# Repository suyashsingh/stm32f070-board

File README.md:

# Hardware Board Design for STM32F070F6
`STM32F070F6` is a 32-bit ARM Cortex-M0 microcontroller from ST. This repository contains the hardware files needed for creating a basic board for working with this micro controller. 

EDA Tool: **KiCad(5.0.1)**.

**Many thanks to [Balram](https://www.linkedin.com/in/balram-jatav/) for helping me out with the PCB design :slightly_smiling_face:**

## Images 
1. Real Board - before assembly

2. 3D View of the Board

3. Fab House Front Copper Layer

4. Board Front Copper Layer

## Board Bring Up Checklist
- [x] 1. Change trace width of power tracks
- [x] 2. Merge `dev` branch to master
- [x] 3. Export gerbers - research about fab houses
- [x] 4. Verify gerbers
- [x] 5. Send board to fab house
- [x] 6. Generate BOM
- [x] 7. Order component and tools

## Timeline
| Event                         | Date          |
| ----------------------------- | ------------- |
| Project Start                 | 12 Sep 2019   |
| Schematic Complete            | 5th Oct 2019  |
| Layout Complete               | 6th Oct 2019  |
| Sent gerbers for fabrication  | 3rd Dec 2019  |
| Received PCB's from fab house | 11th Dec 2019 |
| BOM Complete                  | 17th Dec 2019 |
| Ordered Components & Tools    | 17th Dec 2019 |

## Notes
1. Changed the switches with were earlier decided from *robu.in* to [this](https://in.element14.com/alcoswitch-te-connectivity/fsmsm/switch-spst-0-05a-24vdc-smd/dp/1703878) from element14, as mechanical dimensions were not available.

2. Links that might be useful for usb connector:
	+ [Element 14 Page](https://in.element14.com/molex/47346-0001/usb-conn-2-0-micro-usb-type-b/dp/1568026?st=mirco%20usb%20connector)
	+ [Digi Key Kicad Library](https://github.com/Digi-Key/digikey-kicad-library/tree/master/) - Search for MPN
	+ [Mouser](https://www.mouser.in/ProductDetail/Molex/47346-0001?qs=c2CV6XM0DweJBWaSeyWeCw%3D%3D)

3. Always do a board check when you receive the board from the fab house. You can do:
	
	a. Visual Inspection
	
	b. Check for short between the power rails - This board has 3V3 and 5V power rails. Thanks to Balram for pointing out this.

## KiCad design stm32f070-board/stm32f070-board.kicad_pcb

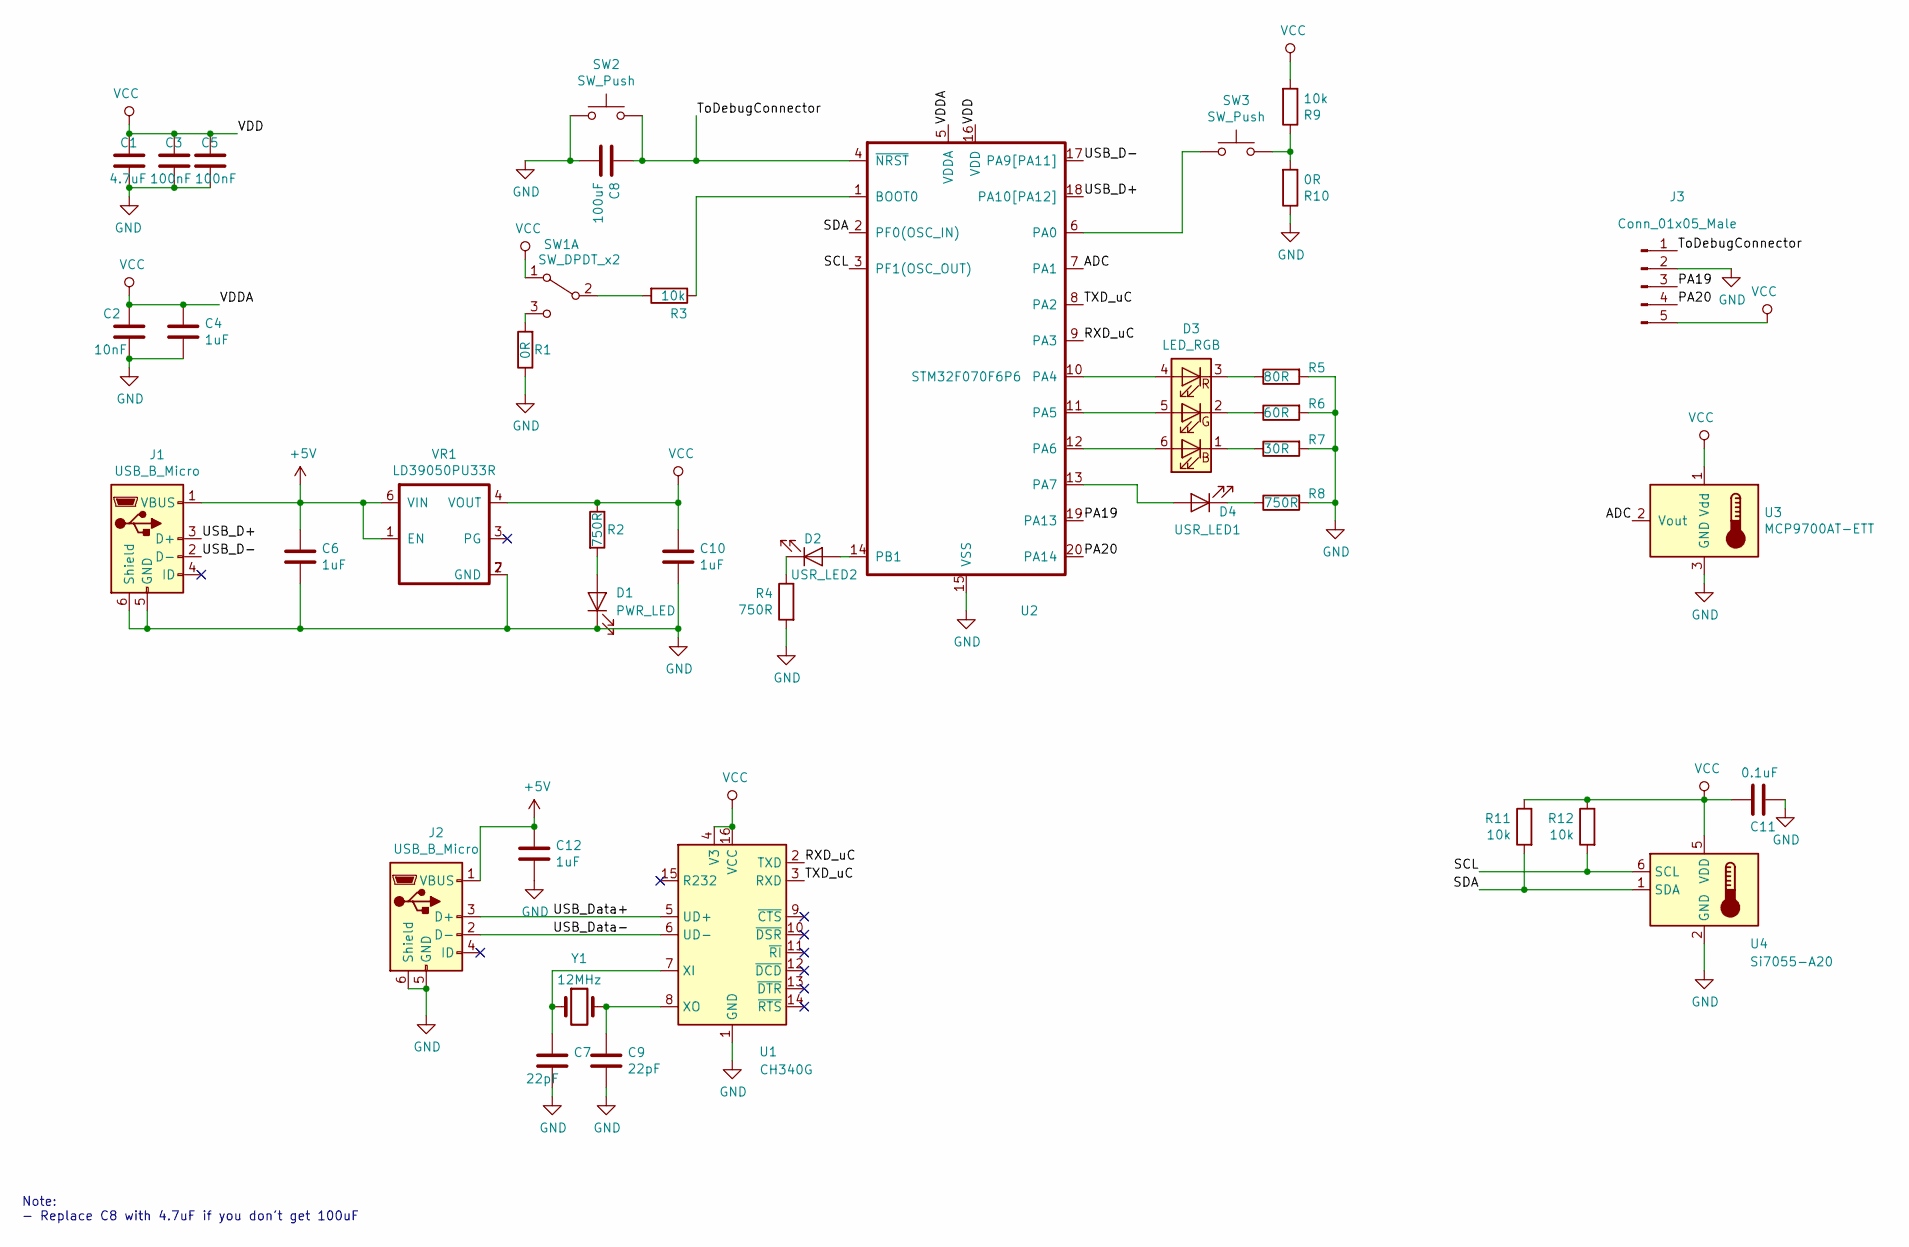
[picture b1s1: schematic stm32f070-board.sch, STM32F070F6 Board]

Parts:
C1: 4.7uF; C_0603_1608Metric_Pad1.05x0.95mm_HandSolder
C2: 10nF; C_0603_1608Metric_Pad1.05x0.95mm_HandSolder
C3, C5: 100nF; C_0603_1608Metric_Pad1.05x0.95mm_HandSolder
C4, C6, C10, C12: 1uF; C_0603_1608Metric_Pad1.05x0.95mm_HandSolder
C7, C9: 22pF; C_0603_1608Metric_Pad1.05x0.95mm_HandSolder
C8: 100uF; C_0603_1608Metric_Pad1.05x0.95mm_HandSolder
C11: 0.1uF; C_0603_1608Metric_Pad1.05x0.95mm_HandSolder
D1: PWR_LED; LED_VISHAY
D2: USR_LED2; LED_VISHAY
D3: LED_RGB; PLCC6
D4: USR_LED1; LED_VISHAY
J1, J2: USB_B_Micro; usb
J3: Conn_01x05_Male; PinHeader_1x05_P1.00mm_Vertical
R1, R10: 0R; R_0603_1608Metric_Pad1.05x0.95mm_HandSolder
R2, R4, R8: 750R; R_0603_1608Metric_Pad1.05x0.95mm_HandSolder
R3, R9, R11, R12: 10k; R_0603_1608Metric_Pad1.05x0.95mm_HandSolder
R5: 80R; R_0603_1608Metric_Pad1.05x0.95mm_HandSolder
R6: 60R; R_0603_1608Metric_Pad1.05x0.95mm_HandSolder
R7: 30R; R_0603_1608Metric_Pad1.05x0.95mm_HandSolder
SW1: SW_DPDT_x2; SLIDE_SWITCH_3.6x9.0mm
SW2, SW3: SW_Push; TACTILE_SWITCH_3.5X6.0mm
U1: CH340G; SOIC-16_3.9x9.9mm_P1.27mm
U2: STM32F070F6P6; TSSOP20_P0.65mm
U3: MCP9700AT-ETT; SOT-23
U4: Si7055-A20; Si705x_Footprint_P1.0mm
VR1: LD39050PU33R; voltage-reg
Y1: 12MHz; HC_49US-(AT49)_1

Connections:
+5V: C6.1, C12.1, J1.1 (VBUS), J2.1 (VBUS), VR1.1 (EN), VR1.6 (VIN)
/ADC: U2.7 (PA1), U3.2 (Vout)
/PA19: J3.3, U2.19 (PA13)
/PA20: J3.4, U2.20 (PA14)
/RXD_uC: U1.2 (TXD), U2.9 (PA3)
/SCL: R12.2, U2.3 (PF1(OSC_OUT)), U4.6 (SCL)
/SDA: R11.2, U2.2 (PF0(OSC_IN)), U4.1 (SDA)
/TXD_uC: U1.3 (RXD), U2.8 (PA2)
/ToDebugConnector: C8.1, J3.1, SW2.2, U2.4 (~NRST)
/USB_D+: J1.3 (D+), U2.18 (PA10[PA12])
/USB_D-: J1.2 (D-), U2.17 (PA9[PA11])
/USB_Data+: J2.3 (D+), U1.5 (UD+)
/USB_Data-: J2.2 (D-), U1.6 (UD-)
GND: C1.2, C2.2, C3.2, C4.2, C5.2, C6.2, C7.2, C8.2, C9.2, C10.2, C11.1, C12.2, D1.1 (K), J1.5 (GND), J1.6 (Shield), J2.5 (GND), J2.6 (Shield), J3.2, R1.1, R4.2, R5.2, R6.2, R7.2, R8.2, R10.1, SW2.1, U1.1 (GND), U2.15 (VSS), U3.3 (GND), U4.2 (GND), VR1.2 (GND), VR1.7 (GND)
unnamed: C7.1, U1.7 (XI), Y1.1
unnamed: C9.1, U1.8 (XO), Y1.2
unnamed: D1.2 (A), R2.2
unnamed: D2.1 (K), R4.1
unnamed: D2.2 (A), U2.14 (PB1)
unnamed: D3.1 (RK), R7.1
unnamed: D3.2 (GK), R6.1
unnamed: D3.3 (BK), R5.1
unnamed: D3.4 (BA), U2.10 (PA4)
unnamed: D3.5 (GA), U2.11 (PA5)
unnamed: D3.6 (RA), U2.12 (PA6)
unnamed: D4.1 (K), R8.1
unnamed: D4.2 (A), U2.13 (PA7)
unnamed: R1.2, SW1.3 (C)
unnamed: R3.1, U2.1 (BOOT0)
unnamed: R3.2, SW1.2 (B)
unnamed: R9.1, R10.2, SW3.2
unnamed: SW3.1, U2.6 (PA0)
VCC: C1.1, C2.1, C3.1, C4.1, C5.1, C10.1, C11.2, J3.5, R2.1, R9.2, R11.1, R12.1, SW1.1 (A), U1.4 (V3), U1.16 (VCC), U2.5 (VDDA), U2.16 (VDD), U3.1 (Vdd), U4.5 (VDD), VR1.4 (VOUT)

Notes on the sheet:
Note: - Replace C8 with 4.7uF if you don't get 100uF

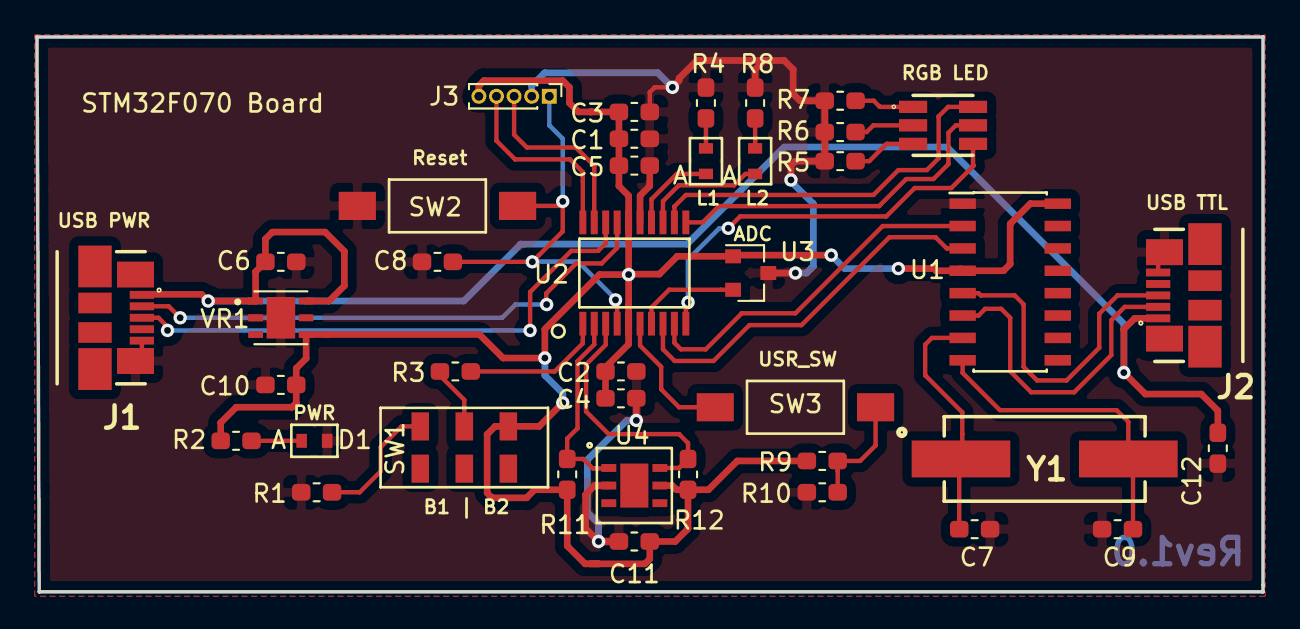
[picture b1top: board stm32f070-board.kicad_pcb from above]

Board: 2 copper layers, 69.6 x 31.5 mm, 40 parts (0 on the bottom side), 33 nets.

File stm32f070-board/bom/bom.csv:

"Id";"Designator";"Package";"Quantity";"Designation";"Supplier and ref";
1;"C12,C4,C6,C10";"C_0603_1608Metric_Pad1.05x0.95mm_HandSolder";4;"1uF";;;
2;"U2";"TSSOP20_P0.65mm";1;"STM32F070F6P6";;;
3;"J3";"PinHeader_1x05_P1.00mm_Vertical";1;"Conn_01x05_Male";;;
4;"U1";"SOIC-16_3.9x9.9mm_P1.27mm";1;"CH340G";;;
5;"U3";"SOT-23";1;"MCP9700AT-ETT";;;
6;"C1";"C_0603_1608Metric_Pad1.05x0.95mm_HandSolder";1;"4.7uF";;;
7;"C2";"C_0603_1608Metric_Pad1.05x0.95mm_HandSolder";1;"10nF";;;
8;"C3,C5";"C_0603_1608Metric_Pad1.05x0.95mm_HandSolder";2;"100nF";;;
9;"C7,C9";"C_0603_1608Metric_Pad1.05x0.95mm_HandSolder";2;"22pF";;;
10;"C8";"C_0603_1608Metric_Pad1.05x0.95mm_HandSolder";1;"100uF";;;
11;"C11";"C_0603_1608Metric_Pad1.05x0.95mm_HandSolder";1;"0.1uF";;;
12;"D1";"LED_VISHAY";1;"PWR_LED";;;
13;"D2";"LED_VISHAY";1;"USR_LED2";;;
14;"D3";"PLCC6";1;"LED_RGB";;;
15;"D4";"LED_VISHAY";1;"USR_LED1";;;
16;"J1,J2";"usb";2;"USB_B_Micro";;;
17;"R1,R10";"R_0603_1608Metric_Pad1.05x0.95mm_HandSolder";2;"0R";;;
18;"R2,R4,R8";"R_0603_1608Metric_Pad1.05x0.95mm_HandSolder";3;"750R";;;
19;"R3,R9,R11,R12";"R_0603_1608Metric_Pad1.05x0.95mm_HandSolder";4;"10k";;;
20;"R5";"R_0603_1608Metric_Pad1.05x0.95mm_HandSolder";1;"80R";;;
21;"R6";"R_0603_1608Metric_Pad1.05x0.95mm_HandSolder";1;"60R";;;
22;"R7";"R_0603_1608Metric_Pad1.05x0.95mm_HandSolder";1;"30R";;;
23;"SW1";"SLIDE_SWITCH_3.6x9.0mm";1;"SW_DPDT_x2";;;
24;"SW2,SW3";"TACTILE_SWITCH_3.5X6.0mm";2;"SW_Push";;;
25;"U4";"Si705x_Footprint_P1.0mm";1;"Si7055-A20";;;
26;"VR1";"voltage-reg";1;"LD39050PU33R";;;
27;"Y1";"HC_49US-(AT49)_1";1;"12MHz";;;

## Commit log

2019-09-12 added initial project files and updated readme.
2019-09-12 created schematic symbol for 3V3 voltage regulator - LD3950
2019-09-12 drafted the 3v3 power supply section using LD3950
2019-09-12 created schematic symbol for STM32F070F6P6
2019-09-12 drafted schematic using STM32FO mcu symbol, added debug
2019-09-12 added connections for user switch and led
2019-09-12 created library for rgb led by modifying inbuild RGB led symbol and added rgb led to the main schematic.
2019-09-12 added temp sensors and ch340 to the schematic
2019-09-13 removed short in boot selector(added a 3way switch) and added zero ohm resistor in the user button.
2019-09-13 added values to the components
2019-09-13 added component values to missing components(cap parallel to the reset switch and user leds)
2019-09-13 replaced 10pin debug connector by 5 pin debug connector - removed redundant pins.
2019-09-13 annoted the schematic
2019-09-26 Added datasheet and product pages to the components
2019-09-26 Changed the user switch SW3 to toggle switch
2019-09-26 Moved all the notes to bottom left of the sheet.
2019-09-26 fixed broken link to product page for 0.1uF capacitor
2019-09-30 Added footprints to passive components
2019-09-30 added foot prints for caps and reistors
2019-09-30 added custom footprint for vishay led.
2019-09-30 added silkscreen layer for vishay led
2019-09-30 added led footprints
2019-09-30 removed old vishay led footprint from the schematic and made changes in the vishay led custom footprint
2019-10-01 Updated schematic
2019-10-04 changed incorrect pin numbers in tssop20 custom package
2019-10-04 added mechanical drawing from ch340g soic16 and updated footprints for stm32 in schematic
2019-10-04 changed the vendor of tactile user switch from robu to element14
2019-10-04 created footprint for tactile switch and updated it in the schematic
2019-10-04 created footprint for the slide switch and updated the same in schematic
2019-10-04 added footprint for rgb led from mouser.
2019-10-04 added footprint for rgb led in schematic
2019-10-04 added free hand drawn courtyard to rgb led and added 1st pin marker on f fab layer
2019-10-04 added footprint for voltage regulator and updated schematic
2019-10-04 added footprint for the crystal and updated it in the schematic
2019-10-04 added footprint for usb cable from mouser.in and added in schematic
2019-10-04 updated footprint for usb connector, created footprint for si705x sensor
2019-10-04 changed the footprint of si705x
2019-10-04 saved the legacy footprint of voltage regulator into new .pretty footprint format and made minor changes to the footprint
2019-10-04 updated the note on the schematic page removed redundant comments
2019-10-04 changed positions of some refdes and values to make things look good
2019-10-05 exported netlist, imported the netlist in pcbnew and created bare board and added netlist import report
2019-10-05 added drc rules fixed the pad near pad error for smd components with fine pitch by setting their pad clearance to 0.004"
2019-10-05 organized components in layout in section wise manner
2019-10-05 first iteration of routing the board -- approx 8 gnd airwires are unrouted evenafter pour
2019-10-06 laid out board on single side, changed the net name to match differential signal conventions in schematic
2019-10-06 Added logos to the pcb layout
2019-10-19 made final cosmetic changes to the pcb
2019-11-27 Removed stray ground trace near the usb jack
2019-11-27 Retouched tracks to make sure they look better
2019-11-29 increased the width of ground and vcc tracks - added net classes
2019-11-29 exported gerber files
2019-11-29 added screenshots of the board
2019-11-29 fixed wigly traces on scl line and near the crystal of ch340
2019-11-29 removed stray arc on f silk screen layer
2019-11-29 added 5v connection to usb jack of ch340(serail converter ic), updated track widths
2019-12-02 Added decoupling capacitor near the usb on ch340 side
2019-12-02 added cacpacitor near usb jack - ch340 side
2019-12-02 made final changes to the pcb layout
2019-12-03 added images of board from fab house
2019-12-03 added acknowledgement
2019-12-03 moved stale master branch to archive directory
2019-12-03 Merged branches: single-side-layout and master
2019-12-03 updated readme with images of the board
2019-12-03 updated readme
    added board bring up checklist and timeline
2019-12-04 added basic bom file
2019-12-17 Added new bom file in open office format
2019-12-17 added pictures of the fabricated board, updated timeline
2019-12-17 updated time line in readme - updated bom
